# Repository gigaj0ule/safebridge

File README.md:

# safebridge

current limited h bridge

contains 3 modules

half bride module (2x)

electronic fuse (1x)

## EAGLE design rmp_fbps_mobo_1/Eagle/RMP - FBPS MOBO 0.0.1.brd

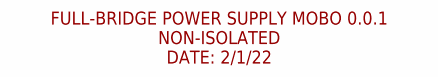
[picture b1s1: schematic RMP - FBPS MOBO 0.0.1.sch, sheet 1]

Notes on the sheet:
FULL-BRIDGE POWER SUPPLY MOBO 0.0.1 NON-ISOLATED DATE: 2/1/22

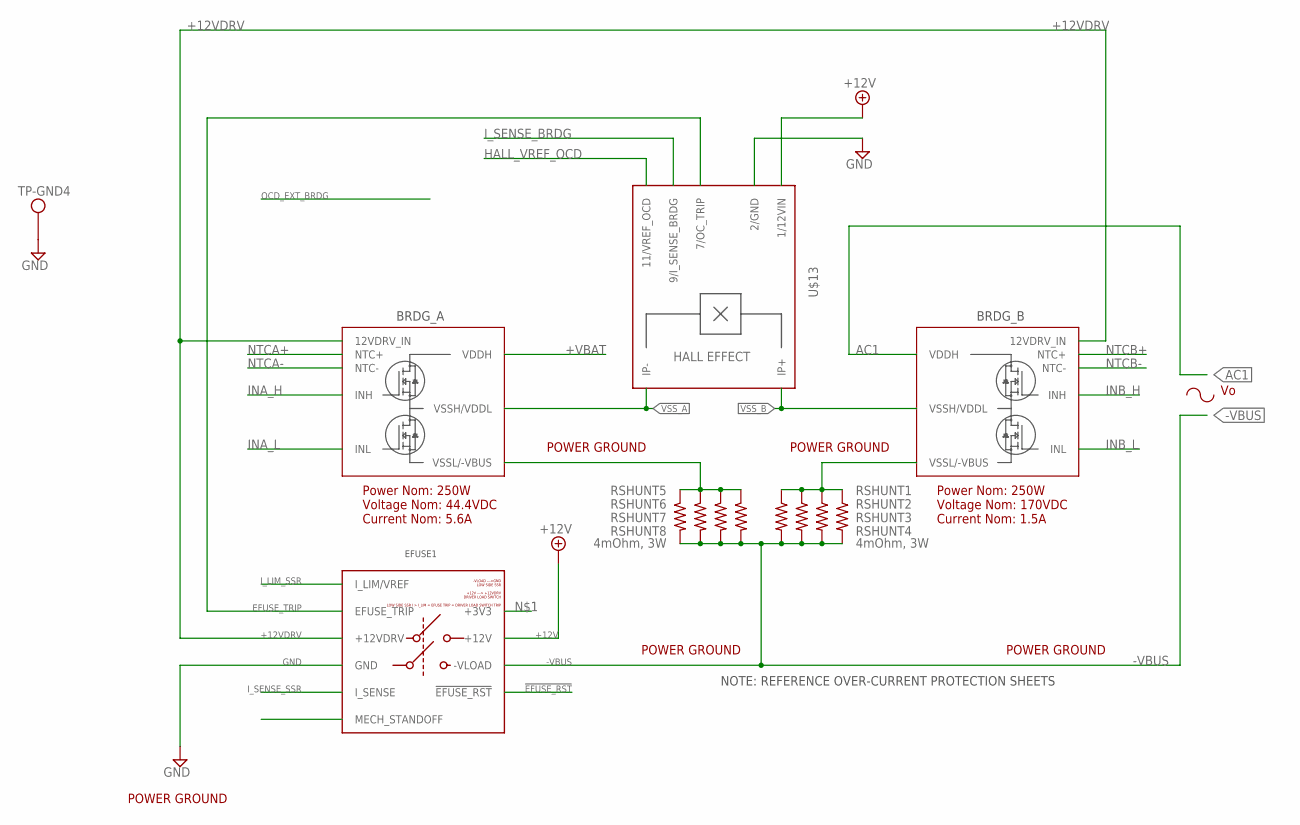
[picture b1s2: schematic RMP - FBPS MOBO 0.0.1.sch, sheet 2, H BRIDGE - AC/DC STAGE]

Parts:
BRDG_A: 1/2BRIDGE; LCSC_PART DNP/CUSTOM
BRDG_B: 1/2BRIDGE; LCSC_PART DNP/CUSTOM
EFUSE1: EFUSE_2.0.0; LCSC_PART DNP/CUSTOM
RSHUNT1, RSHUNT2, RSHUNT3, RSHUNT4, RSHUNT5, RSHUNT6, RSHUNT7, RSHUNT8: 4mOhm, 3W; R2512; LCSC_PART C728322
TP-GND4: THM_TESTPOINT_5000_SERIES; THM-TESTPOINT; LCSC_PART DNP
U$13: HALL_EFFECT_CURRENT_MONITOR; HALL_CURRENT_MONITOR; LCSC_PART DNP/CUSTOM

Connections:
!EFUSE_RST: EFUSE1.12/!EFUSE_RST (!EFUSE_RST); also elsewhere on the board
+12V: EFUSE1.11/12VIN (+12V), U$13.1/+12VIN (1/12VIN); also elsewhere on the board
+12VDRV: BRDG_A.11/+12DRVR (12VDRV_IN), BRDG_B.11/+12DRVR (12VDRV_IN), EFUSE1.12/12VDRV (+12VDRV)
+VBAT: BRDG_A.1/VDDA (VDDH), BRDG_A.2/VDDA (VDDH), BRDG_A.3/VDDA (VDDH), BRDG_A.4/VDDA (VDDH); also elsewhere on the board
-VBUS: EFUSE1.1/-VLOAD (-VLOAD), EFUSE1.2/-VLOAD (-VLOAD), EFUSE1.3/-VLOAD (-VLOAD), EFUSE1.4/-VLOAD (-VLOAD), EFUSE1.5/-VLOAD (-VLOAD), EFUSE1.6/-VLOAD (-VLOAD), EFUSE1.7/-VLOAD (-VLOAD), EFUSE1.8/-VLOAD (-VLOAD), RSHUNT1.2, RSHUNT2.2, RSHUNT3.2, RSHUNT4.2, RSHUNT5.2, RSHUNT6.2, RSHUNT7.2, RSHUNT8.2; also elsewhere on the board
AC1: BRDG_B.1/VDDA (VDDH), BRDG_B.2/VDDA (VDDH), BRDG_B.3/VDDA (VDDH), BRDG_B.4/VDDA (VDDH); also elsewhere on the board
EFUSE_TRIP: EFUSE1.10/EFUSE_TRIP (EFUSE_TRIP), U$13.7/EFUSE_TRIP (7/OC_TRIP); also elsewhere on the board
GND: EFUSE1.1/GND (GND), EFUSE1.2/GND (GND), EFUSE1.3/GND (GND), EFUSE1.4/GND (GND), EFUSE1.5/GND (GND), EFUSE1.6/GND (GND), EFUSE1.7/GND (GND), EFUSE1.8/GND (GND), EFUSE1.9/GND (GND), TP-GND4.P1, U$13.2/GND, U$13.3/GND (2/GND); also elsewhere on the board
HALL_VREF_OCD: U$13.11/VREF_OCD
INA_H: BRDG_A.10/IN_H (INH); also elsewhere on the board
INA_L: BRDG_A.9/IN_L (INL); also elsewhere on the board
INB_H: BRDG_B.10/IN_H (INH); also elsewhere on the board
INB_L: BRDG_B.9/IN_L (INL); also elsewhere on the board
I_LIM_SSR: EFUSE1.11/VREF (I_LIM/VREF); also elsewhere on the board
I_SENSE_BRDG: U$13.9/I_SENSE_BRDG; also elsewhere on the board
I_SENSE_SSR: EFUSE1.9/-VLOAD_SW (I_SENSE); also elsewhere on the board
unnamed: BRDG_A.9/-VBUS (VSSL/-VBUS), BRDG_A.10/-VBUS (VSSL/-VBUS), BRDG_A.11/-VBUS (VSSL/-VBUS), BRDG_A.12/-VBUS (VSSL/-VBUS), RSHUNT5.1, RSHUNT6.1, RSHUNT7.1, RSHUNT8.1
unnamed: BRDG_B.9/-VBUS (VSSL/-VBUS), BRDG_B.10/-VBUS (VSSL/-VBUS), BRDG_B.11/-VBUS (VSSL/-VBUS), BRDG_B.12/-VBUS (VSSL/-VBUS), RSHUNT1.1, RSHUNT2.1, RSHUNT3.1, RSHUNT4.1
unnamed: EFUSE1.S1 (MECH_STANDOFF), EFUSE1.S2 (MECH_STANDOFF)
NTCA+: BRDG_A.7/NTC+ (NTC+); also elsewhere on the board
NTCA-: BRDG_A.8/NTC- (NTC-); also elsewhere on the board
NTCB+: BRDG_B.7/NTC+ (NTC+); also elsewhere on the board
NTCB-: BRDG_B.8/NTC- (NTC-); also elsewhere on the board
VSS_A: BRDG_A.1/VSSA (VSSH/VDDL), BRDG_A.2/VSSA (VSSH/VDDL), BRDG_A.3/VSSA (VSSH/VDDL), BRDG_A.4/VSSA (VSSH/VDDL), U$13.7/IP- (IP-), U$13.8/IP- (IP-), U$13.9/IP- (IP-), U$13.10/IP- (IP-), U$13.11/IP- (IP-), U$13.12/IP- (IP-); also elsewhere on the board
VSS_B: BRDG_B.1/VSSA (VSSH/VDDL), BRDG_B.2/VSSA (VSSH/VDDL), BRDG_B.3/VSSA (VSSH/VDDL), BRDG_B.4/VSSA (VSSH/VDDL), U$13.1/IP+ (IP+), U$13.2/IP+ (IP+), U$13.3/IP+ (IP+), U$13.4/IP+ (IP+), U$13.5/IP+ (IP+), U$13.6/IP+ (IP+); also elsewhere on the board

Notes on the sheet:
NOTE: REFERENCE OVER-CURRENT PROTECTION SHEETS
Power Nom: 250W Voltage Nom: 170VDC Current Nom: 1.5A
Power Nom: 250W Voltage Nom: 44.4VDC Current Nom: 5.6A
POWER GROUND

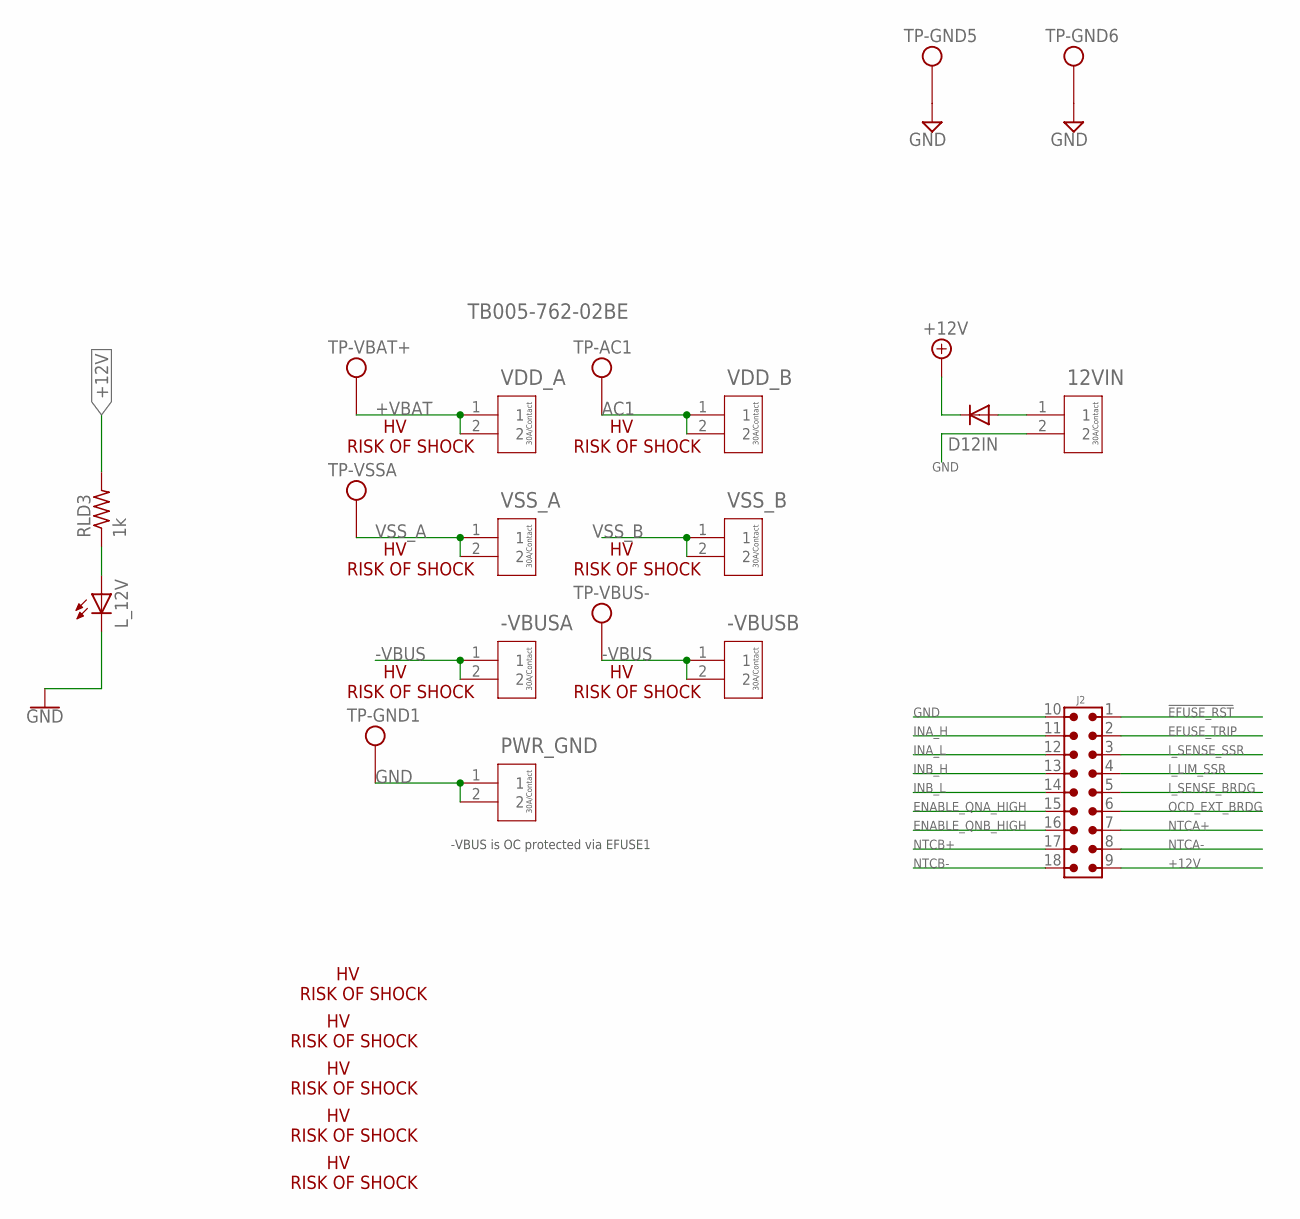
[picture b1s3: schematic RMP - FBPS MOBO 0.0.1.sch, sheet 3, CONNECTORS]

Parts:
12VIN: TB005-762-02BE; TB005-762-02BE_CUD; LCSC_PART DNP
-VBUSA: TB005-762-02BE; TB005-762-02BE_CUD; LCSC_PART DNP
-VBUSB: TB005-762-02BE; TB005-762-02BE_CUD; LCSC_PART DNP
D12IN: DIODESMA; SMADIODE; LCSC_PART C110531
J2: 6620XX21022_66201821022; 66201821022; LCSC_PART DNP
L_12V: LEDCHIPLED_1206; CHIPLED_1206; LCSC_PART C434439
PWR_GND: TB005-762-02BE; TB005-762-02BE_CUD; LCSC_PART DNP
RLD3: 1k; R1206; LCSC_PART C115421
TP-AC1: THM_TESTPOINT_5000_SERIES; THM-TESTPOINT; LCSC_PART DNP
TP-GND1, TP-GND5, TP-GND6: THM_TESTPOINT_5000_SERIES; THM-TESTPOINT; LCSC_PART DNP
TP-VBAT+: THM_TESTPOINT_5000_SERIES; THM-TESTPOINT; LCSC_PART DNP
TP-VBUS-: THM_TESTPOINT_5000_SERIES; THM-TESTPOINT; LCSC_PART DNP
TP-VSSA: THM_TESTPOINT_5000_SERIES; THM-TESTPOINT; LCSC_PART DNP
U$1, U$2, U$3, U$4, U$5, U$6, U$7, U$8, U$9, U$10, U$11: ELECTRIC_SHOCK; LCSC_PART DNP
VDD_A: TB005-762-02BE; TB005-762-02BE_CUD; LCSC_PART DNP
VDD_B: TB005-762-02BE; TB005-762-02BE_CUD; LCSC_PART DNP
VSS_A: TB005-762-02BE; TB005-762-02BE_CUD; LCSC_PART DNP
VSS_B: TB005-762-02BE; TB005-762-02BE_CUD; LCSC_PART DNP

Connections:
!EFUSE_RST: J2.1; also elsewhere on the board
+12V: D12IN.C, J2.9, RLD3.2; also elsewhere on the board
+VBAT: TP-VBAT+.P1, VDD_A.1, VDD_A.2; also elsewhere on the board
-VBUS: -VBUSA.1, -VBUSA.2, -VBUSB.1, -VBUSB.2, TP-VBUS-.P1; also elsewhere on the board
AC1: TP-AC1.P1, VDD_B.1, VDD_B.2; also elsewhere on the board
EFUSE_TRIP: J2.2; also elsewhere on the board
ENABLE_QNA_HIGH: J2.15
ENABLE_QNB_HIGH: J2.16
GND: 12VIN.2, J2.10, L_12V.C, PWR_GND.1, PWR_GND.2, TP-GND1.P1, TP-GND5.P1, TP-GND6.P1; also elsewhere on the board
INA_H: J2.11; also elsewhere on the board
INA_L: J2.12; also elsewhere on the board
INB_H: J2.13; also elsewhere on the board
INB_L: J2.14; also elsewhere on the board
I_LIM_SSR: J2.4; also elsewhere on the board
I_SENSE_BRDG: J2.5; also elsewhere on the board
I_SENSE_SSR: J2.3; also elsewhere on the board
unnamed: 12VIN.1, D12IN.A
unnamed: L_12V.A, RLD3.1
NTCA+: J2.7; also elsewhere on the board
NTCA-: J2.8; also elsewhere on the board
NTCB+: J2.17; also elsewhere on the board
NTCB-: J2.18; also elsewhere on the board
OCD_EXT_BRDG: J2.6
VSS_A: TP-VSSA.P1, VSS_A.1, VSS_A.2; also elsewhere on the board
VSS_B: VSS_B.1, VSS_B.2; also elsewhere on the board

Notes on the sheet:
-VBUS is OC protected via EFUSE1

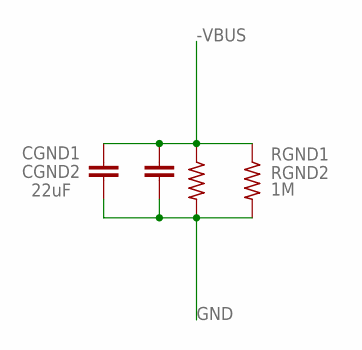
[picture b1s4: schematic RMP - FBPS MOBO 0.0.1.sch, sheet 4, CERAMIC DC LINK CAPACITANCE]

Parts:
CGND1, CGND2: 22uF; C1206; LCSC_PART DNP/C77091
RGND1, RGND2: 1M; R1206; LCSC_PART DNP/C26124

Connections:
-VBUS: CGND1.1, CGND2.1, RGND1.1, RGND2.1; also elsewhere on the board
GND: CGND1.2, CGND2.2, RGND1.2, RGND2.2; also elsewhere on the board

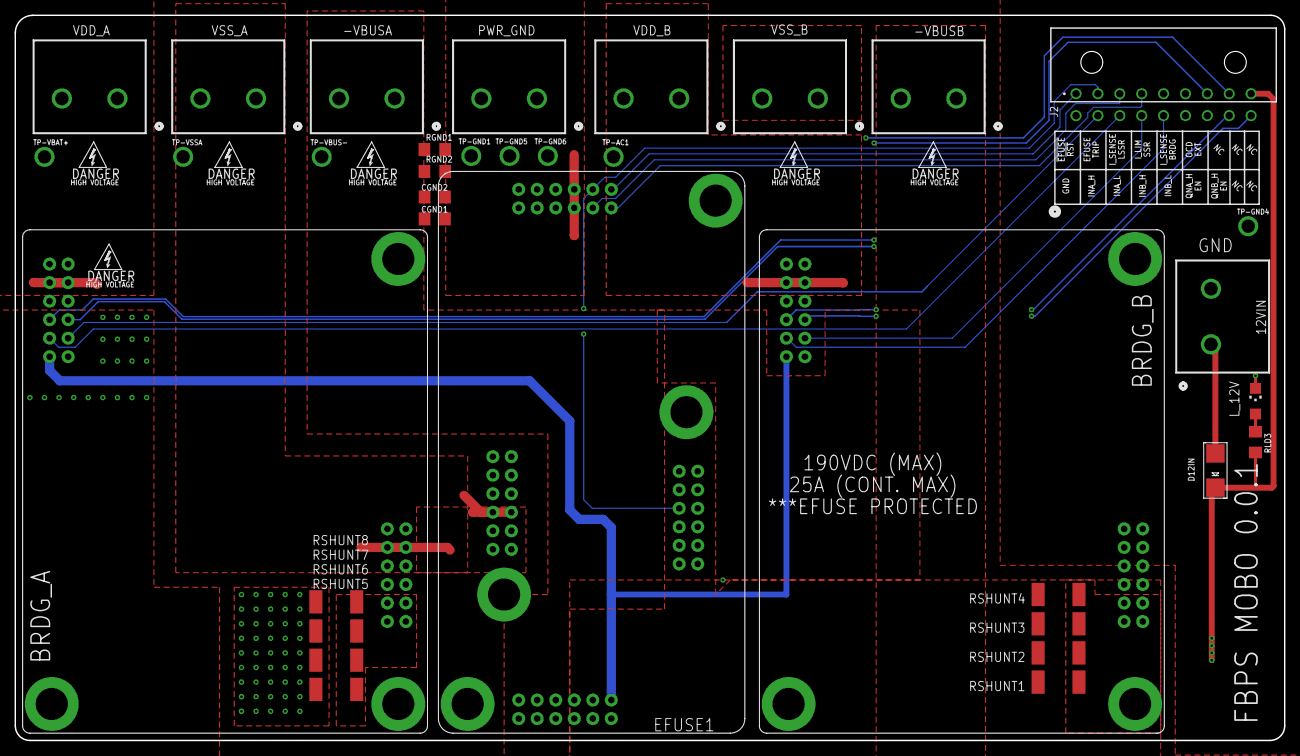
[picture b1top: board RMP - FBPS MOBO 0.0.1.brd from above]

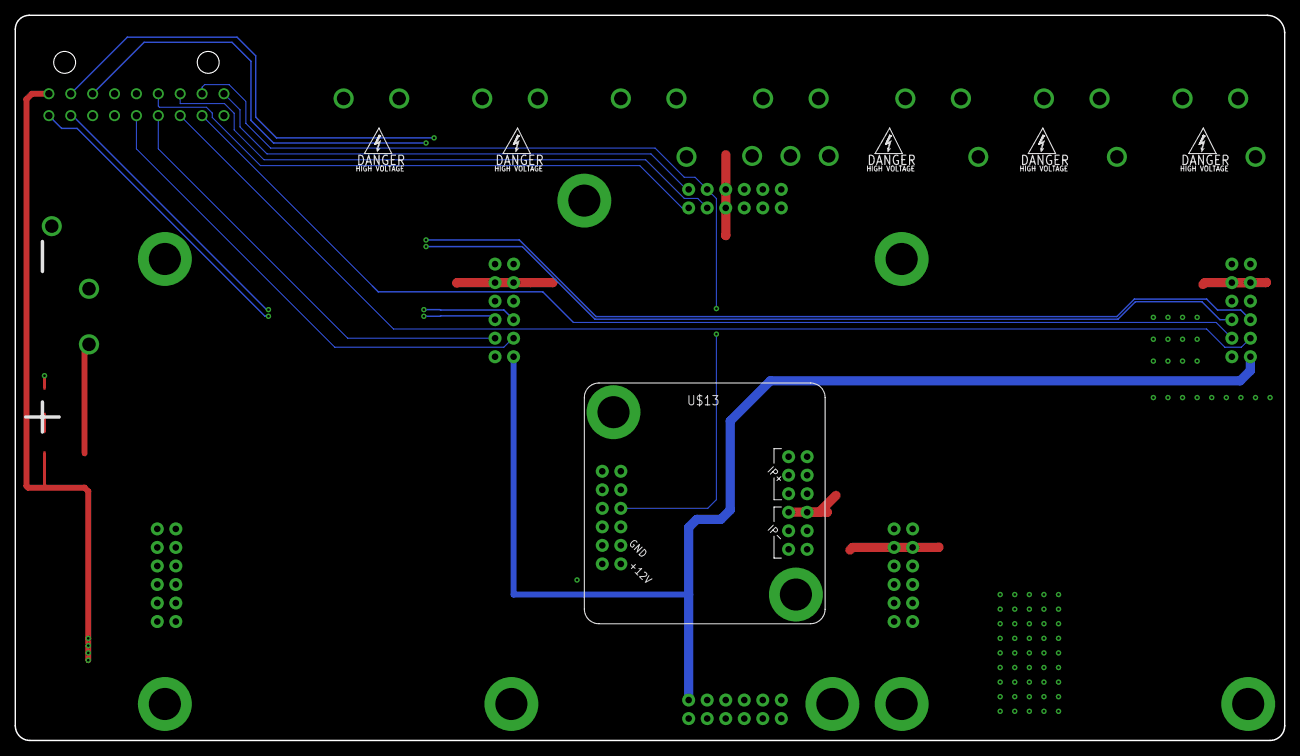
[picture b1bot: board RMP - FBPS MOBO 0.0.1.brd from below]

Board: 4 copper layers, 174.0 x 99.4 mm, 47 parts (6 on the bottom side), 26 nets.

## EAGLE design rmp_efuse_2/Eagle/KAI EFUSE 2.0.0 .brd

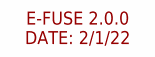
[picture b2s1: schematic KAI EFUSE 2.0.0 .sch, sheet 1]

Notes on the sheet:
E-FUSE 2.0.0 DATE: 2/1/22

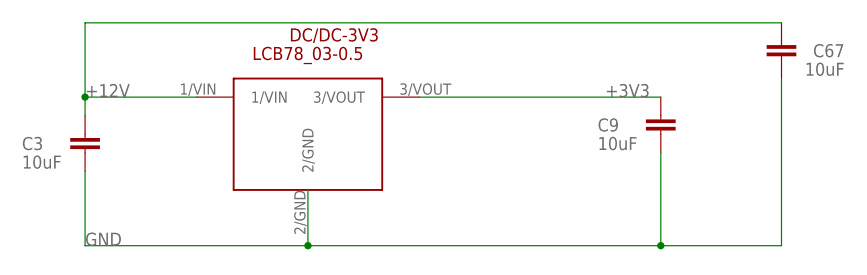
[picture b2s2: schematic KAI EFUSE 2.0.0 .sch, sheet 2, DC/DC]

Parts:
C3, C9, C67: 10uF; C1206; LCSC_PART C13585
DC/DC-3V3: LCB78_03-0.5; 3-SIP; LCSC_PART DNP

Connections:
+3V3: C9.2, DC/DC-3V3.3/VOUT; also elsewhere on the board
+12V: C3.2, C67.2, DC/DC-3V3.1/VIN; also elsewhere on the board
GND: C3.1, C9.1, C67.1, DC/DC-3V3.2/GND; also elsewhere on the board

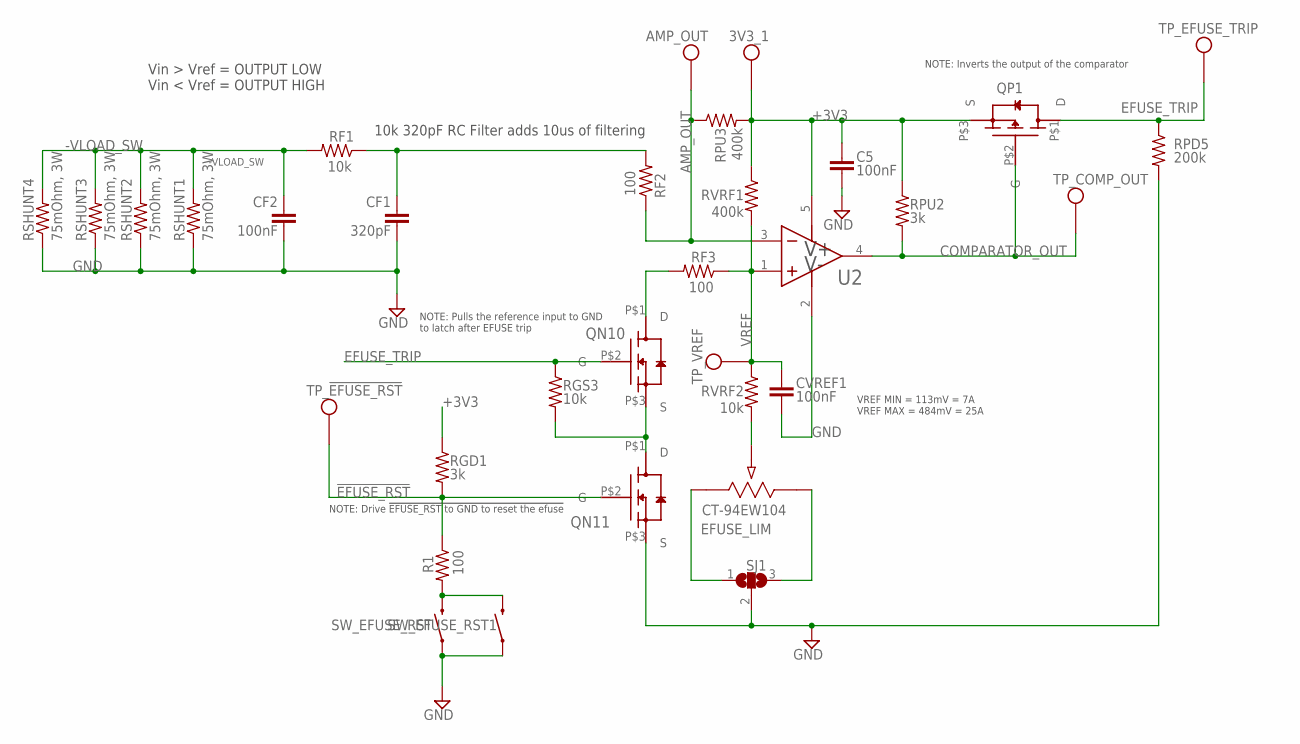
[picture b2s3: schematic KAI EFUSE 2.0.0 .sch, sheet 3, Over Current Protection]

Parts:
3V3_1: THM_TESTPOINT_5000_SERIES; THM-TESTPOINT
AMP_OUT: THM_TESTPOINT_5000_SERIES; THM-TESTPOINT
C5: 100nF; C0603; LCSC_PART C14663
CF1: 320pF; C0603; LCSC_PART C14663
CF2: 100nF; C0603; LCSC_PART C14663
CVREF1: 100nF; C0603; LCSC_PART C14663
EFUSE_LIM: CT-94EW104; POT_CT-94EW_NDC; LCSC_PART DNP
QN10, QN11: NFET-(SOT-23-3)(TO-236-3)(SC-59); SOT23,SC-59,TO-236-3; LCSC_PART C296286
QP1: PFET-(SOT-23-3)(TO-236-3)(SC-59); SOT23,SC-59,TO-236-3; LCSC_PART C489594
R1: 100; R0603; LCSC_PART C103197
RF1: 10k; R0603; LCSC_PART C491175
RF2, RF3: 100; R0603; LCSC_PART C103197
RGD1: 3k; R0603; LCSC_PART C126358
RGS3: 10k; R0603; LCSC_PART C116677
RPD5: 200k; R0603; LCSC_PART C95331
RPU2: 3k; R0603; LCSC_PART C126358
RPU3: 400k; R0603; LCSC_PART C209133
RSHUNT1, RSHUNT2, RSHUNT3, RSHUNT4: 75mOhm, 3W; R2512; LCSC_PART C459689
RVRF1: 400k; R0603; LCSC_PART C209133
RVRF2: 10k; R0603; LCSC_PART C116677
SJ1: SJ2W; SJ_2; LCSC_PART DNP
SW_EFUSE_RST, SW_EFUSE_RST1: MOMENTARY-SWITCH-SPST-SMD-6.0X3.5MM; TACTILE_SWITCH_SMD_6.0X3.5MM; LCSC_PART C520860
TP_!EFUSE_RST: THM_TESTPOINT_5000_SERIES; THM-TESTPOINT
TP_COMP_OUT: THM_TESTPOINT_5000_SERIES; THM-TESTPOINT
TP_EFUSE_TRIP: THM_TESTPOINT_5000_SERIES; THM-TESTPOINT
TP_VREF: THM_TESTPOINT_5000_SERIES; THM-TESTPOINT
U2: LMV331M5X; MF05A; LCSC_PART C253067

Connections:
!EFUSE_RST: QN11.P$2 (G), R1.1, RGD1.2, TP_!EFUSE_RST.P1; also elsewhere on the board
+3V3: 3V3_1.P1, C5.1, QP1.P$3 (S), RGD1.1, RPU2.1, RPU3.2, RVRF1.1, U2.5 (V+); also elsewhere on the board
-VLOAD_SW: CF2.1, RF1.2, RSHUNT1.2, RSHUNT2.2, RSHUNT3.2, RSHUNT4.2; also elsewhere on the board
AMP_OUT: AMP_OUT.P1, RF2.1, RPU3.1, U2.3 (IN-)
COMPARATOR_OUT: QP1.P$2 (G), RPU2.2, TP_COMP_OUT.P1, U2.4 (OUT)
EFUSE_TRIP: QN10.P$2 (G), QP1.P$1 (D), RGS3.1, RPD5.1, TP_EFUSE_TRIP.P1; also elsewhere on the board
GND: C5.2, CF1.2, CF2.2, CVREF1.2, QN11.P$3 (S), RPD5.2, RSHUNT1.1, RSHUNT2.1, RSHUNT3.1, RSHUNT4.1, SJ1.2, SW_EFUSE_RST.1, SW_EFUSE_RST1.1, U2.2 (V-); also elsewhere on the board
unnamed: QN10.P$1 (D), RF3.2
unnamed: QN10.P$3 (S), QN11.P$1 (D), RGS3.2
unnamed: R1.2, SW_EFUSE_RST.2, SW_EFUSE_RST1.2
unnamed: EFUSE_LIM.2, RVRF2.2
unnamed: EFUSE_LIM.1, SJ1.1
unnamed: EFUSE_LIM.3, SJ1.3
VOUTB: CF1.1, RF1.1, RF2.2
VREF: CVREF1.1, RF3.1, RVRF1.2, RVRF2.1, TP_VREF.P1, U2.1 (IN+); also elsewhere on the board

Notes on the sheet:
Vin > Vref = OUTPUT LOW Vin < Vref = OUTPUT HIGH
NOTE: Pulls the reference input to GND to latch after EFUSE trip
NOTE: Inverts the output of the comparator
NOTE: Drive !EFUSE_RST to GND to reset the efuse
10k 320pF RC Filter adds 10us of filtering
VREF MIN = 113mV = 7A VREF MAX = 484mV = 25A

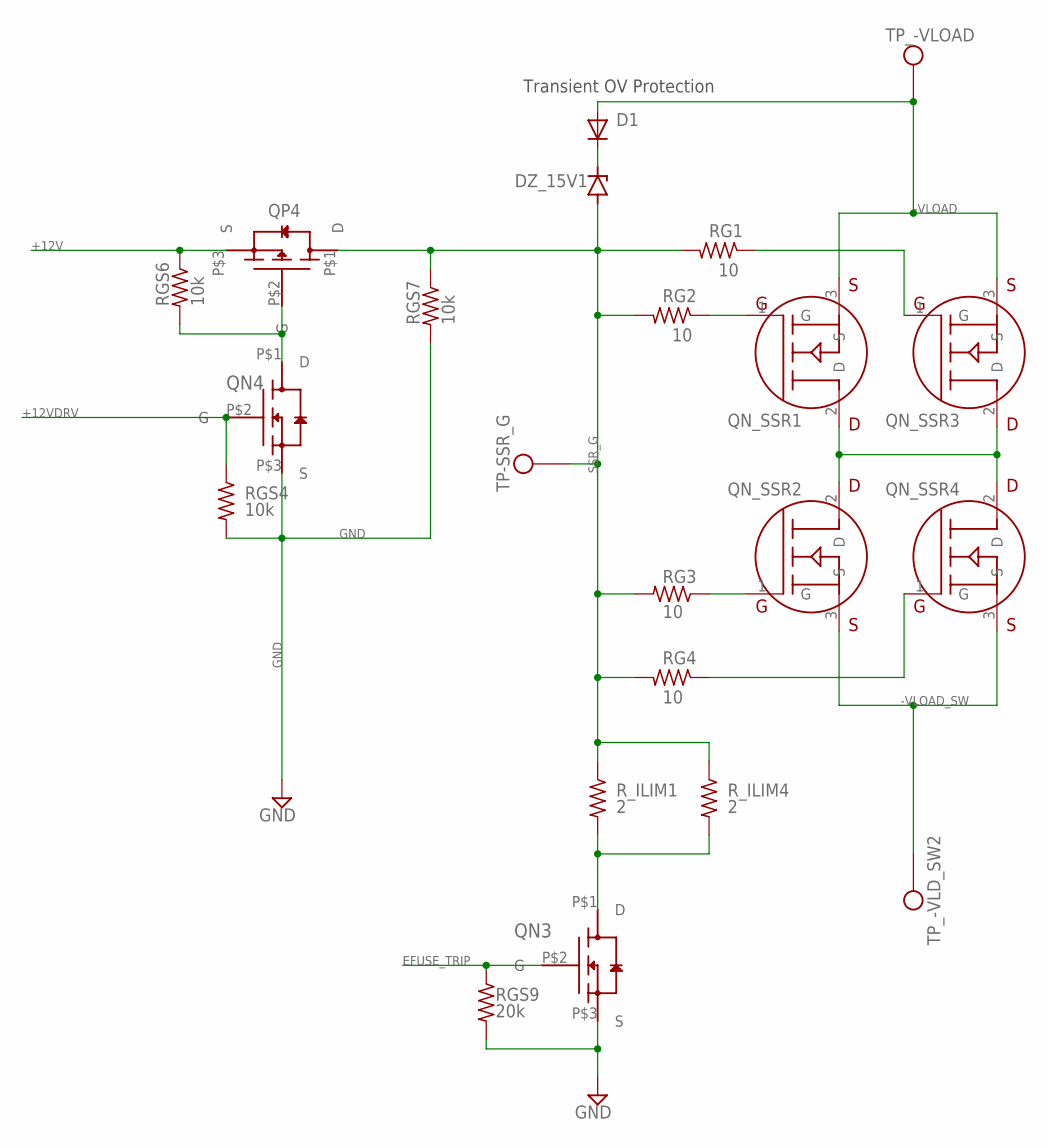
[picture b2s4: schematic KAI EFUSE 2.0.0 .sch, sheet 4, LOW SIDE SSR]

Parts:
D1: DIODESMA; SMADIODE; LCSC_PART C110531
DZ_15V1: NZH15B,115; SODFL3718X115; LCSC_PART C173428
QN3, QN4: NFET-(SOT-23-3)(TO-236-3)(SC-59); SOT23,SC-59,TO-236-3; LCSC_PART C296286
QN_SSR1, QN_SSR2, QN_SSR3, QN_SSR4: IPB60R060P7ATMA1; D2PACK; LCSC_PART DNP
QP4: PFET-(SOT-23-3)(TO-236-3)(SC-59); SOT23,SC-59,TO-236-3; LCSC_PART C489594
RG1, RG2, RG3, RG4: 10; R1206; LCSC_PART C326706
RGS4, RGS6, RGS7: 10k; R0603; LCSC_PART C116677
RGS9: 20k; R0603; LCSC_PART C118368
R_ILIM1, R_ILIM4: 2; R1206; LCSC_PART C102322
TP-SSR_G: THM_TESTPOINT_5000_SERIES; THM-TESTPOINT
TP_-VLD_SW2: THM_TESTPOINT_5000_SERIES; THM-TESTPOINT
TP_-VLOAD: THM_TESTPOINT_5000_SERIES; THM-TESTPOINT

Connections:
+12V: QP4.P$3 (S), RGS6.1; also elsewhere on the board
+12VDRV: QN4.P$2 (G), RGS4.1; also elsewhere on the board
-VLOAD: D1.A, QN_SSR1.3 (S), QN_SSR3.3 (S), TP_-VLOAD.P1; also elsewhere on the board
-VLOAD_SW: QN_SSR2.3 (S), QN_SSR4.3 (S), TP_-VLD_SW2.P1; also elsewhere on the board
EFUSE_TRIP: QN3.P$2 (G), RGS9.1; also elsewhere on the board
GND: QN3.P$3 (S), QN4.P$3 (S), RGS4.2, RGS7.2, RGS9.2; also elsewhere on the board
unnamed: QN4.P$1 (D), QP4.P$2 (G), RGS6.2
unnamed: D1.C, DZ_15V1.1 (C)
unnamed: QN_SSR2.1 (G), RG3.1
unnamed: QN_SSR3.1 (G), RG1.1
unnamed: QN_SSR4.1 (G), RG4.1
unnamed: QN_SSR1.1 (G), RG2.1
unnamed: QN3.P$1 (D), R_ILIM1.2, R_ILIM4.2
SSR_G: DZ_15V1.2 (A), QP4.P$1 (D), RG1.2, RG2.2, RG3.2, RG4.2, RGS7.1, R_ILIM1.1, R_ILIM4.1, TP-SSR_G.P1
VSS_A1: QN_SSR1.2 (D), QN_SSR2.2 (D), QN_SSR3.2 (D), QN_SSR4.2 (D)

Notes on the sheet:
Transient OV Protection

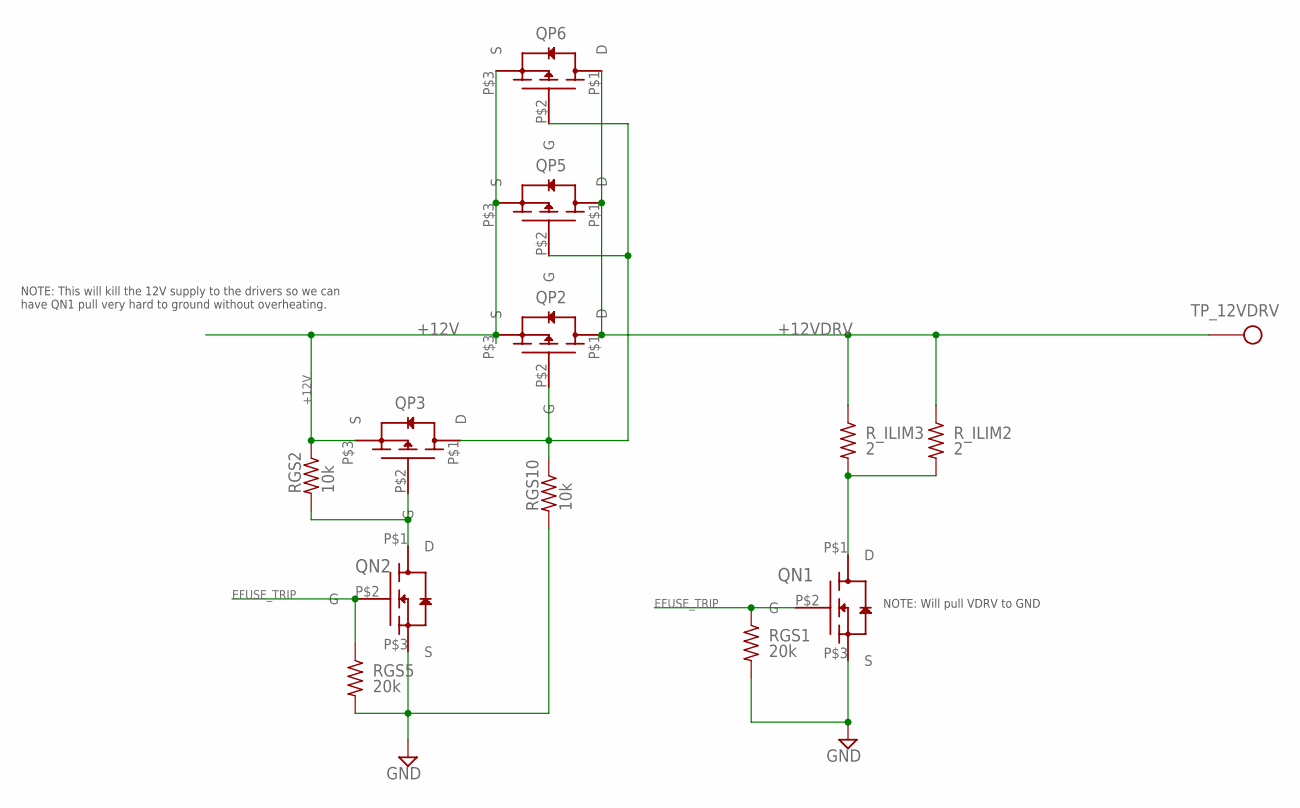
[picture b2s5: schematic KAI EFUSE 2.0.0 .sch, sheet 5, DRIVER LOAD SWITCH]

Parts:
QN1, QN2: NFET-(SOT-23-3)(TO-236-3)(SC-59); SOT23,SC-59,TO-236-3; LCSC_PART C296286
QP2, QP3, QP5, QP6: PFET-(SOT-23-3)(TO-236-3)(SC-59); SOT23,SC-59,TO-236-3; LCSC_PART C489594
RGS1, RGS5: 20k; R0603; LCSC_PART C118368
RGS2, RGS10: 10k; R0603; LCSC_PART C116677
R_ILIM2, R_ILIM3: 2; R1206; LCSC_PART C102322
TP_12VDRV: THM_TESTPOINT_5000_SERIES; THM-TESTPOINT

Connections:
+12V: QP2.P$3 (S), QP3.P$3 (S), QP5.P$3 (S), QP6.P$3 (S), RGS2.1; also elsewhere on the board
+12VDRV: QP2.P$1 (D), QP5.P$1 (D), QP6.P$1 (D), R_ILIM2.1, R_ILIM3.1, TP_12VDRV.P1; also elsewhere on the board
EFUSE_TRIP: QN1.P$2 (G), QN2.P$2 (G), RGS1.1, RGS5.1; also elsewhere on the board
GND: QN1.P$3 (S), QN2.P$3 (S), RGS1.2, RGS5.2, RGS10.2; also elsewhere on the board
unnamed: QP2.P$2 (G), QP3.P$1 (D), QP5.P$2 (G), QP6.P$2 (G), RGS10.1
unnamed: QN2.P$1 (D), QP3.P$2 (G), RGS2.2
OUTA_H: QN1.P$1 (D), R_ILIM2.2, R_ILIM3.2

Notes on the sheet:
NOTE: This will kill the 12V supply to the drivers so we can have QN1 pull very hard to ground without overheating.
NOTE: Will pull VDRV to GND

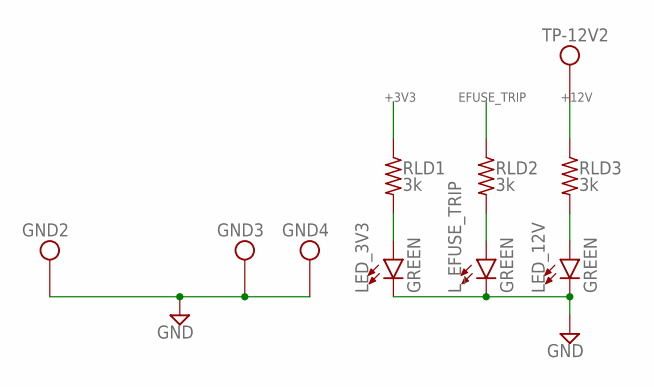
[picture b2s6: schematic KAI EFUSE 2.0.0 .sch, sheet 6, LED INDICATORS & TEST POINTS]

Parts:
GND2, GND3, GND4: THM_TESTPOINT_5000_SERIES; THM-TESTPOINT
LED_3V3, LED_12V: GREEN; LED-1206; LCSC_PART C434439
L_EFUSE_TRIP: GREEN; LED-1206; LCSC_PART C434439
RLD1, RLD2, RLD3: 3k; R0603; LCSC_PART C126358
TP-12V2: THM_TESTPOINT_5000_SERIES; THM-TESTPOINT

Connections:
+3V3: RLD1.1; also elsewhere on the board
+12V: RLD3.1, TP-12V2.P1; also elsewhere on the board
EFUSE_TRIP: RLD2.1; also elsewhere on the board
GND: GND2.P1, GND3.P1, GND4.P1, LED_3V3.C, LED_12V.C, L_EFUSE_TRIP.C; also elsewhere on the board
unnamed: LED_3V3.A, RLD1.2
unnamed: L_EFUSE_TRIP.A, RLD2.2
unnamed: LED_12V.A, RLD3.2

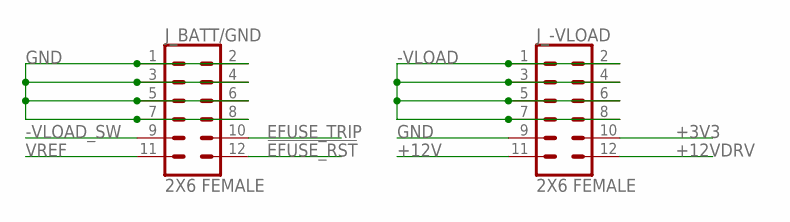
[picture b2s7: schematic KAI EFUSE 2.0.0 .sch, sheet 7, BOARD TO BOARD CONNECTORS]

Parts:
J_-VLOAD: 2X6 FEMALE; 2X6; LCSC_PART DNP
J_BATT/GND: 2X6 FEMALE; 2X6; LCSC_PART DNP

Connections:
!EFUSE_RST: J_BATT/GND.12; also elsewhere on the board
+3V3: J_-VLOAD.10; also elsewhere on the board
+12V: J_-VLOAD.11; also elsewhere on the board
+12VDRV: J_-VLOAD.12; also elsewhere on the board
-VLOAD: J_-VLOAD.1, J_-VLOAD.2, J_-VLOAD.3, J_-VLOAD.4, J_-VLOAD.5, J_-VLOAD.6, J_-VLOAD.7, J_-VLOAD.8; also elsewhere on the board
-VLOAD_SW: J_BATT/GND.9; also elsewhere on the board
EFUSE_TRIP: J_BATT/GND.10; also elsewhere on the board
GND: J_-VLOAD.9, J_BATT/GND.1, J_BATT/GND.2, J_BATT/GND.3, J_BATT/GND.4, J_BATT/GND.5, J_BATT/GND.6, J_BATT/GND.7, J_BATT/GND.8; also elsewhere on the board
VREF: J_BATT/GND.11; also elsewhere on the board

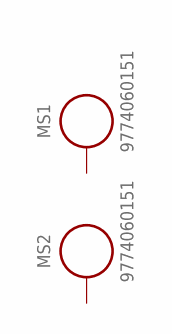
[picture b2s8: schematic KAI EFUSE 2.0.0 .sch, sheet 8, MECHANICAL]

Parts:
MS1, MS2: 9774060151; WA-SMSI_9774060151; LCSC_PART DNP

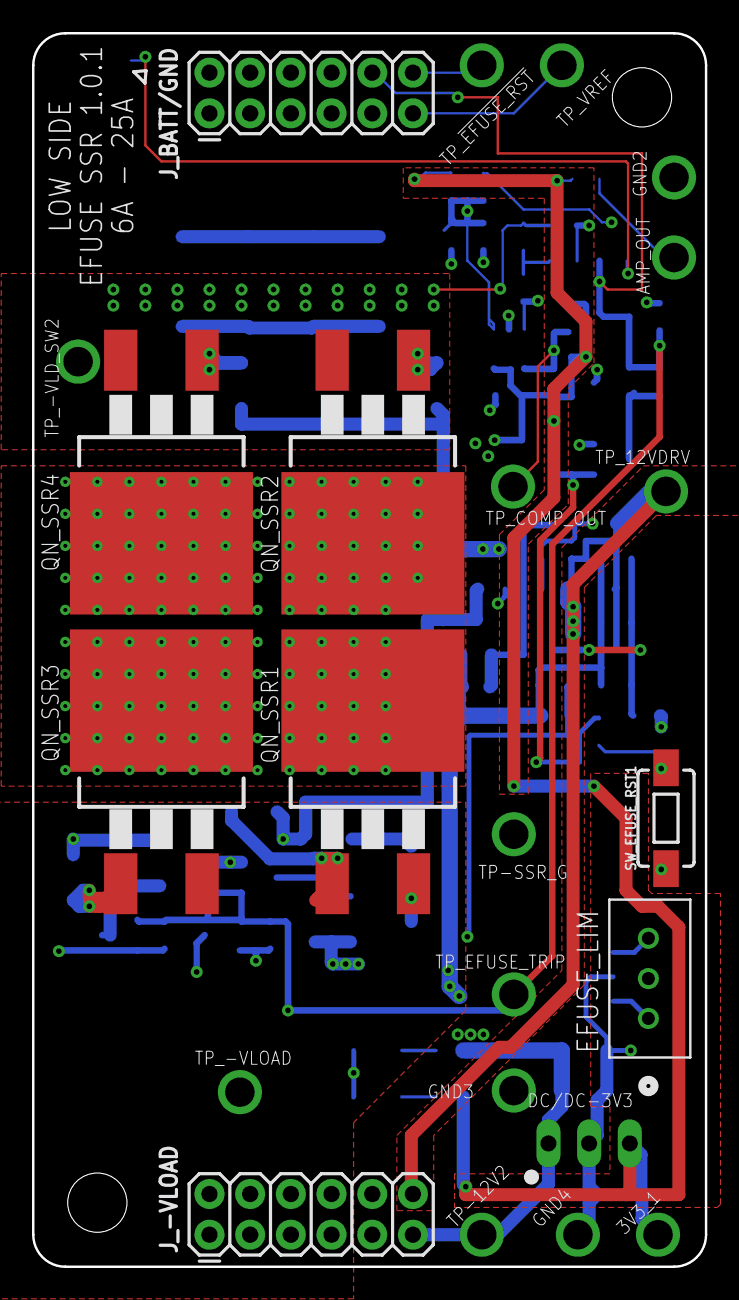
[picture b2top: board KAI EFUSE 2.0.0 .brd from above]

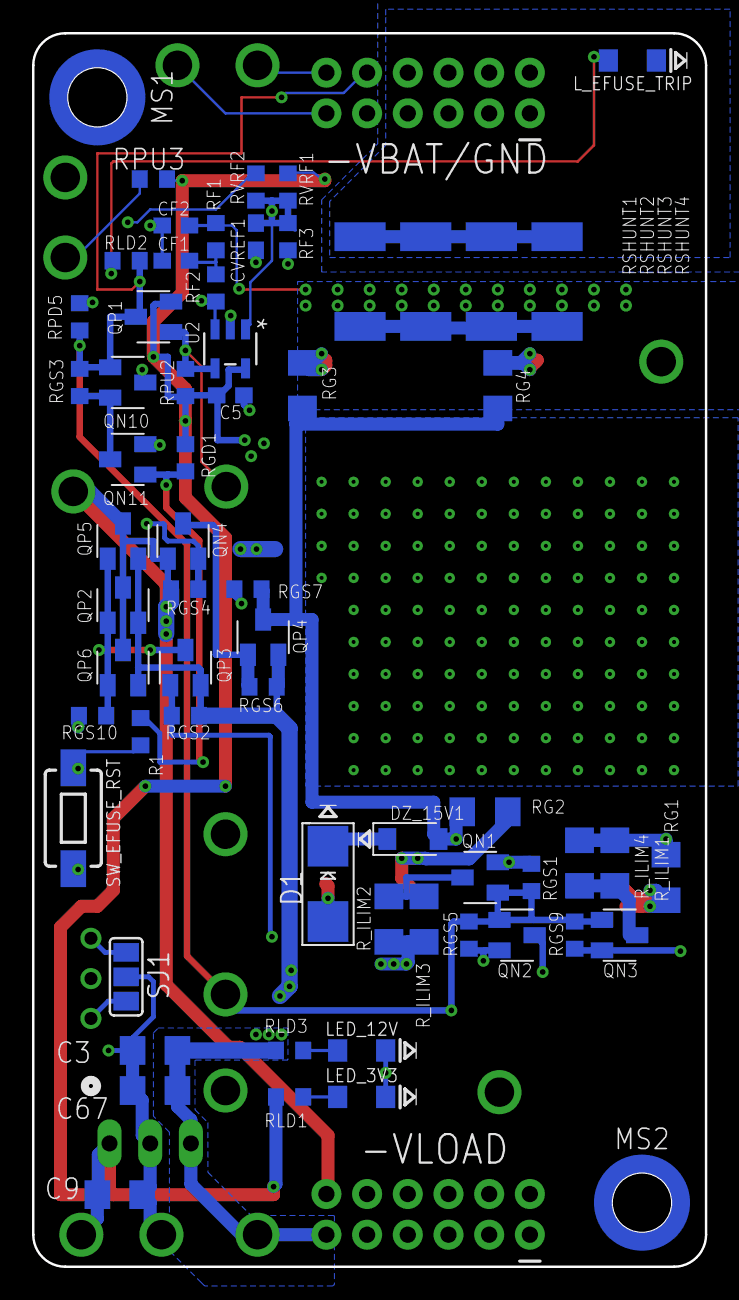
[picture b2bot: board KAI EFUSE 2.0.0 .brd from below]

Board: 4 copper layers, 42.0 x 77.0 mm, 86 parts (63 on the bottom side), 33 nets.

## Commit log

2022-04-21 first commit in independent repo

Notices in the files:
parts and their libraries:
SparkFun-LED: Licensing: Creative Commons ShareAlike 4.0 International - https://creativecommons.org/licenses/by-sa/4.0
Eagle_WA-SMSI: Copyright: Würth Elektronik
COPYRIGHT: Copyright (C) 2021 Ultra Librarian. All rights reserved.
